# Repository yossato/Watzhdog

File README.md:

# Watzhdog
This device wakes you up when you fall a sleep while you are meeting, studing or working, using a vibration motor.

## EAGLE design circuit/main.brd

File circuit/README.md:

## License  
Copyright (c) 2018, Yoshiaki Sato  
<br />This work is licensed under a <a rel="license" href="http://creativecommons.org/licenses/by-sa/4.0/">Creative Commons Attribution-ShareAlike 4.0 International License</a>.

(c) i.Design Studio 2014
(c) Sparkfun Electronics 2015, 2016

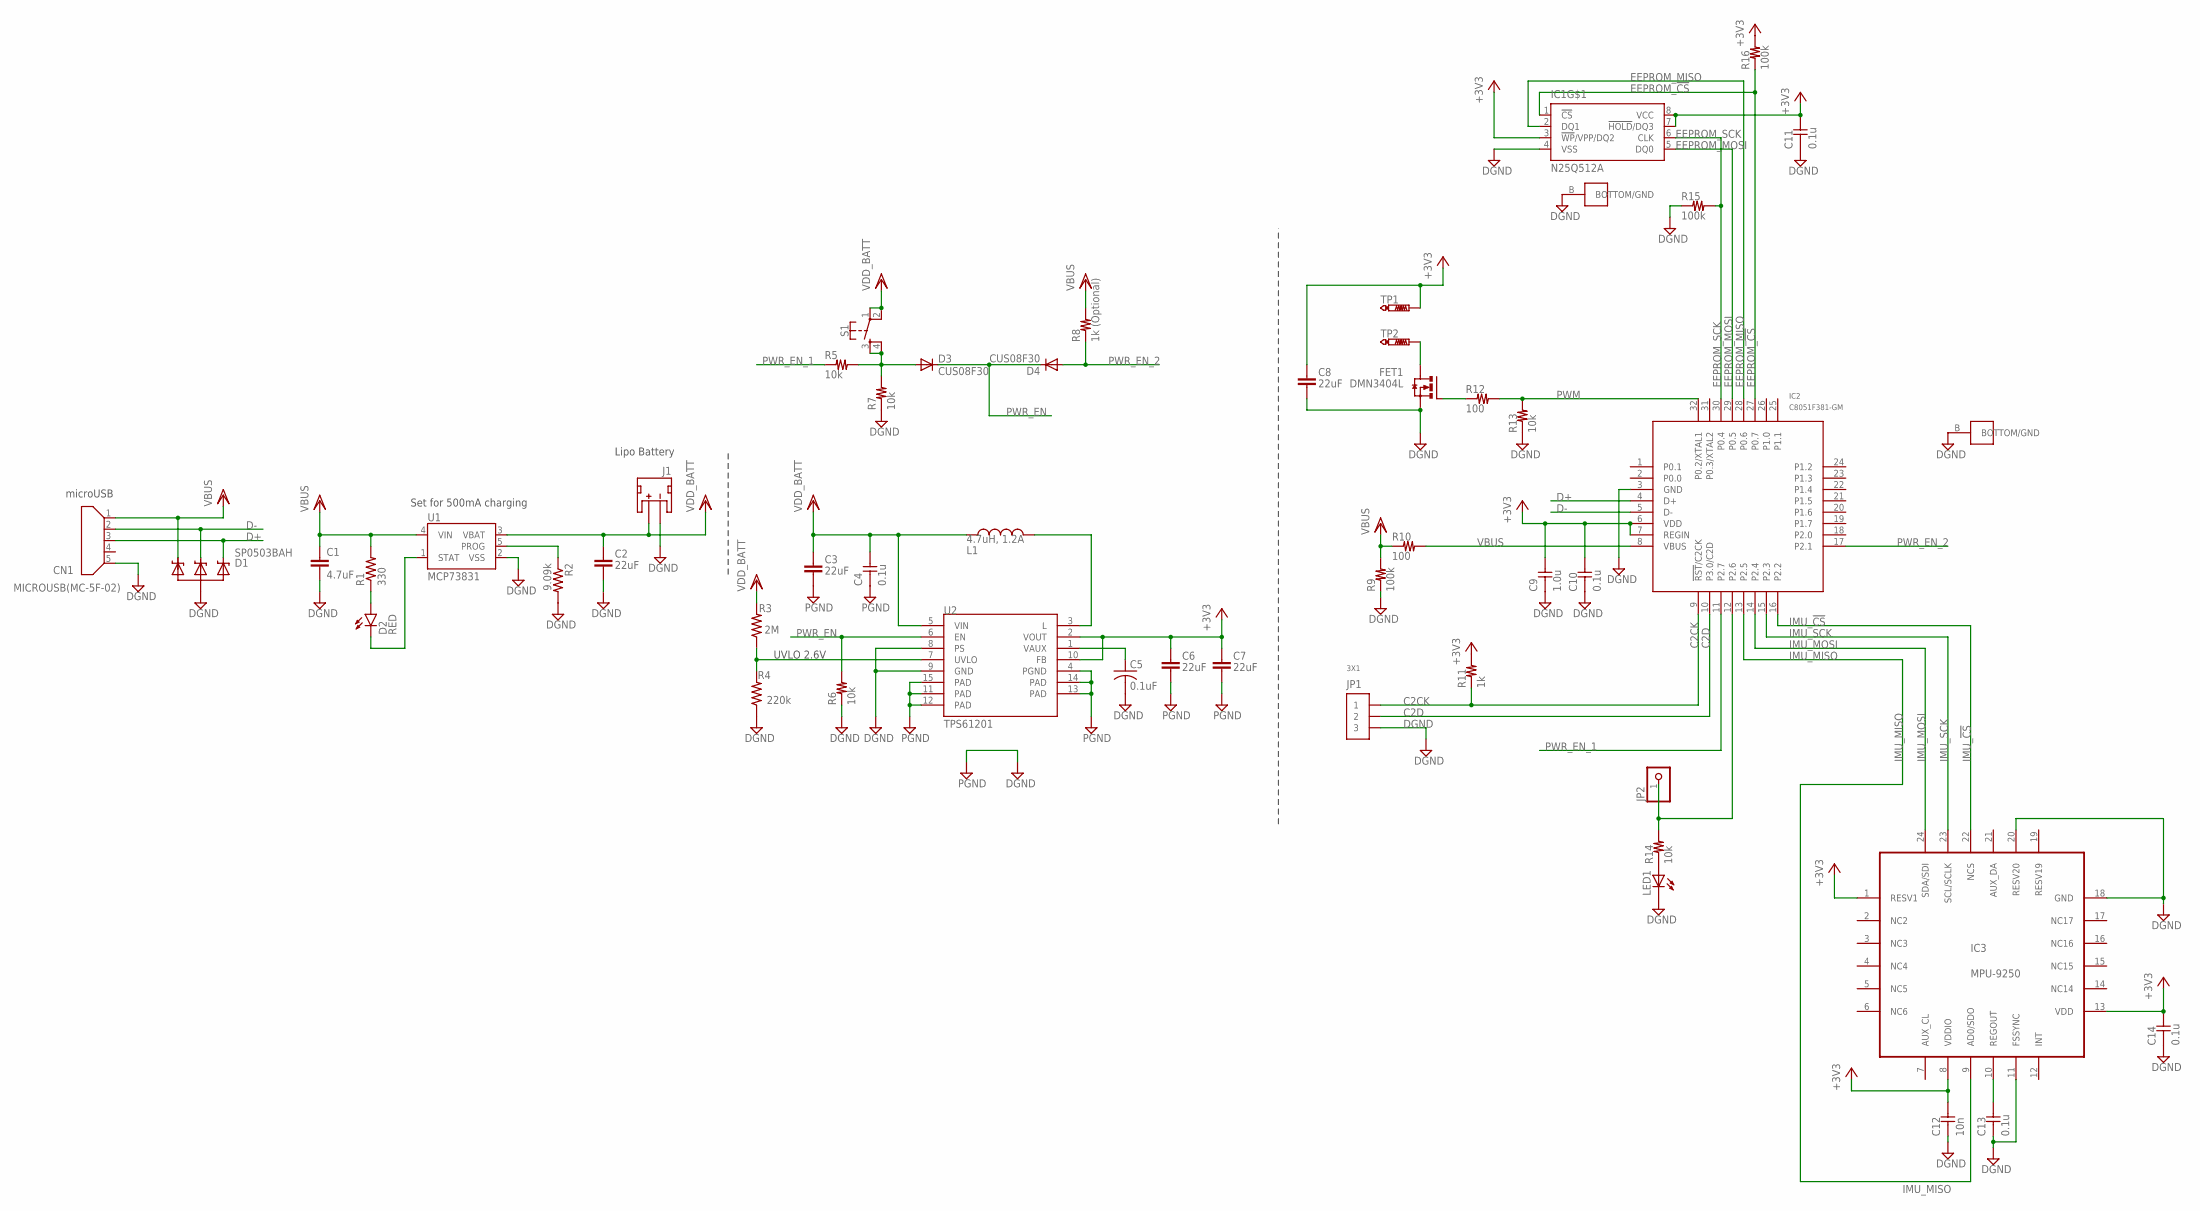
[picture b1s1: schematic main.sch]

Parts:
C1: 4.7uF; 0603-CAP
C2, C3, C6, C7, C8: 22uF; 0805
C4, C10, C11, C13, C14: 0.1u; 1005
C5: 0.1uF; C0402K
C9: 1.0u; 1005
C12: 10n; 1005
CN1: MICROUSB(MC-5F-02)
D1: SP0503BAH; SOT143
D2: RED; LED-0603
D3, D4: CUS08F30; SOD323-W
FET1: DMN3404L; SOT23
IC1: N25Q512A; V-PDFN-8
IC2: C8051F381-GM; QFN32
IC3: MPU-9250; QFN-24
J1: JST; JST-2-SMD
JP1: 3X1; MA3-1
JP2: PINHD-1X1; 1X01
L1: 4.7uH, 1.2A; CDRH2D09
LED1: LED1608O; 1608-OLI
R1: 330; R0402
R2: 9.09k; R0402
R3: 2M; R0402
R4: 220k; R0402
R5, R6, R7, R13, R14: 10k; 1005
R8: 1k (Optional); 1005
R9, R15, R16: 100k; 1005
R10, R12: 100; 1005
R11: 1k; 1005
S1: MOMENTARY-SWITCH-SPST-2-SMD-4.6X2.8MM; TACTILE_SWITCH_SMD_4.6X2.8MM
TP1, TP2: PTR1TP10R; TP10R
U1: MCP73831; SOT23-5
U2: TPS61201; QFN-10_PAD

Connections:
+3V3: C6.1, C7.1, C8.1, C9.P$2, C10.P$2, C11.P$2, C12.P$2, C14.P$2, IC1.3 (!WP!/VPP/DQ2), IC1.7 (!HOLD!/DQ3), IC1.8 (VCC), IC2.6 (VDD), IC2.7 (REGIN), IC3.1 (RESV1), IC3.8 (VDDIO), IC3.13 (VDD), R11.P$2, R16.P$2, TP1.TP, U2.2 (VOUT), U2.10 (FB)
C2CK: IC2.9 (!RST!/C2CK), JP1.1, R11.P$1
C2D: IC2.10 (P3.0/C2D), JP1.2
D+: CN1.3, D1.2, IC2.4 (D+)
D-: CN1.2, D1.3, IC2.5 (D-)
DGND: C1.2, C2.2, C3.2, C4.P$1, C5.2, C6.2, C7.2, C8.2, C9.P$1, C10.P$1, C11.P$1, C12.P$1, C13.P$1, C14.P$1, CN1.5, D1.1, FET1.S, IC1.4 (VSS), IC1.B (BOTTOM/GND), IC2.3 (GND), IC2.B (BOTTOM/GND), IC3.11 (FSSYNC), IC3.18 (GND), IC3.20 (RESV20), J1.1 (-), JP1.3, LED1.K, R2.2, R4.1, R6.P$1, R7.P$1, R9.P$1, R13.P$1, R15.P$1, U1.2 (VSS), U2.4 (PGND), U2.8 (PS), U2.9 (GND), U2.11 (PAD), U2.12 (PAD), U2.13 (PAD), U2.14 (PAD), U2.15 (PAD)
EEPROM_!CS: IC1.1 (!CS), IC2.27 (P0.7), R16.P$1
EEPROM_MISO: IC1.2 (DQ1), IC2.28 (P0.6)
EEPROM_MOSI: IC1.5 (DQ0), IC2.29 (P0.5)
EEPROM_SCK: IC1.6 (CLK), IC2.30 (P0.4), R15.P$2
IMU_!CS: IC2.16 (P2.2), IC3.22 (NCS)
IMU_MISO: IC2.13 (P2.5), IC3.9 (AD0/SDO)
IMU_MOSI: IC2.14 (P2.4), IC3.24 (SDA/SDI)
IMU_SCK: IC2.15 (P2.3), IC3.23 (SCL/SCLK)
LIN: L1.P$1 (1), U2.3 (L)
unnamed: D2.A, R1.1
unnamed: FET1.G, R12.P$1
unnamed: LED1.A, R14.P$1
unnamed: FET1.D, TP2.TP
unnamed: D3.A, R5.P$2, R7.P$2, S1.3, S1.4
unnamed: C13.P$2, IC3.10 (REGOUT)
unnamed: IC2.12 (P2.6), JP2.1, R14.P$2
unnamed: IC2.8 (VBUS), R10.P$2
PROG: R2.1, U1.5 (PROG)
PWM: IC2.32 (P0.2/XTAL1), R12.P$2, R13.P$2
PWR_EN: D3.C, D4.C, R6.P$2, U2.6 (EN)
PWR_EN_1: IC2.11 (P2.7), R5.P$1
PWR_EN_2: D4.A, IC2.17 (P2.1), R8.P$1
STAT: D2.C, U1.1 (STAT)
UVLO: R3.1, R4.2, U2.7 (UVLO)
VAUX: C5.1, U2.1 (VAUX)
VBUS: C1.1, CN1.1, D1.4, R1.2, R8.P$2, R9.P$2, R10.P$1, U1.4 (VIN)
VDD_BATT: C2.1, C3.1, C4.P$2, J1.2 (+), L1.P$2 (2), R3.2, S1.1, S1.2, U1.3 (VBAT), U2.5 (VIN)

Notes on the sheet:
Set for 500mA charging
microUSB
Lipo Battery
UVLO 2.6V

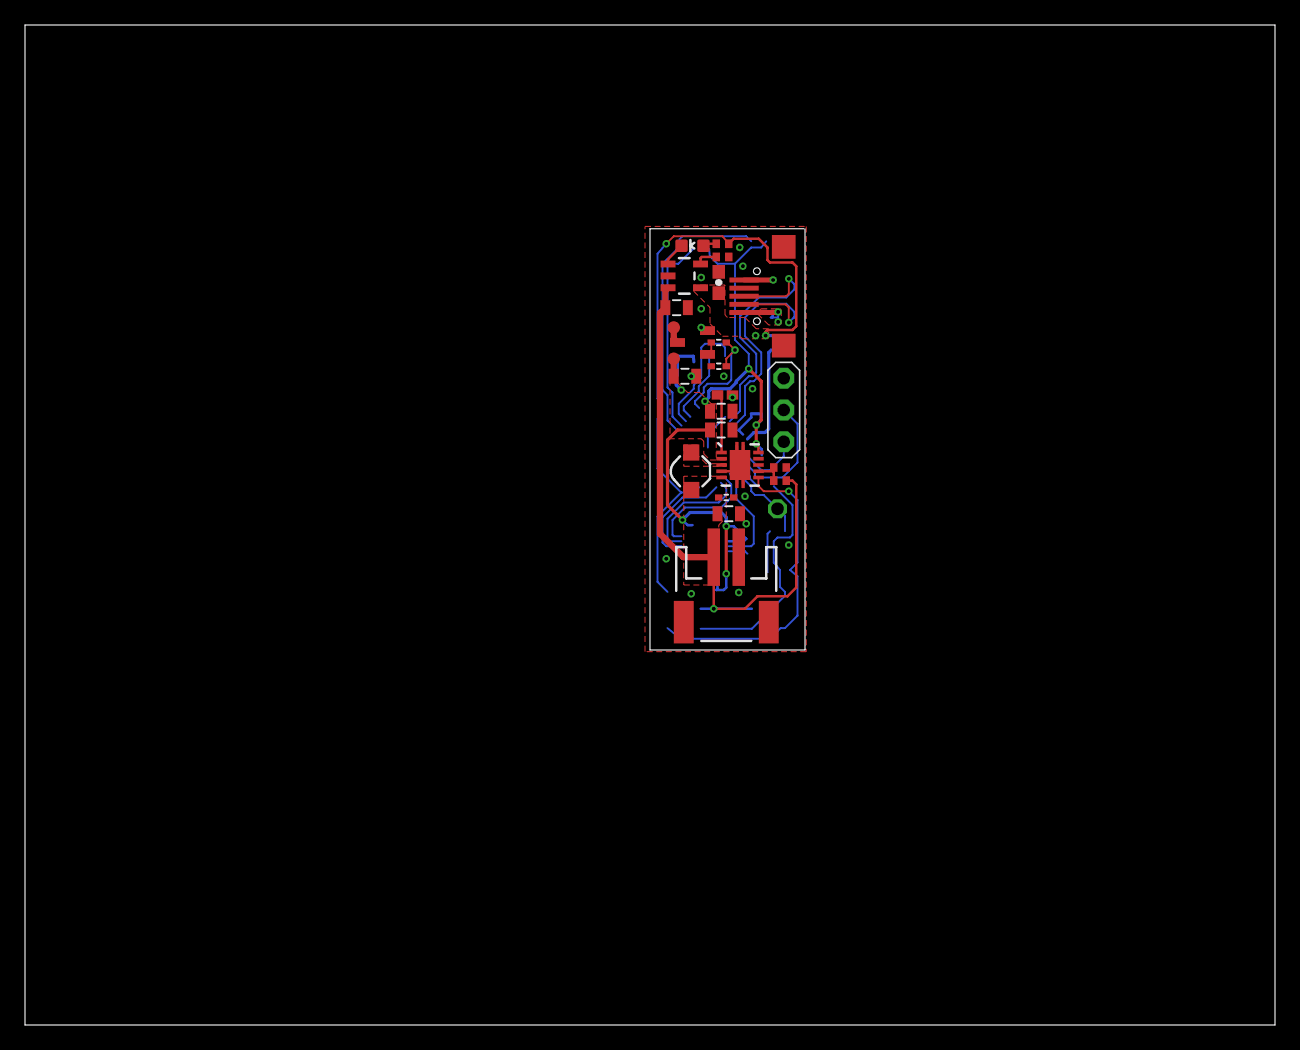
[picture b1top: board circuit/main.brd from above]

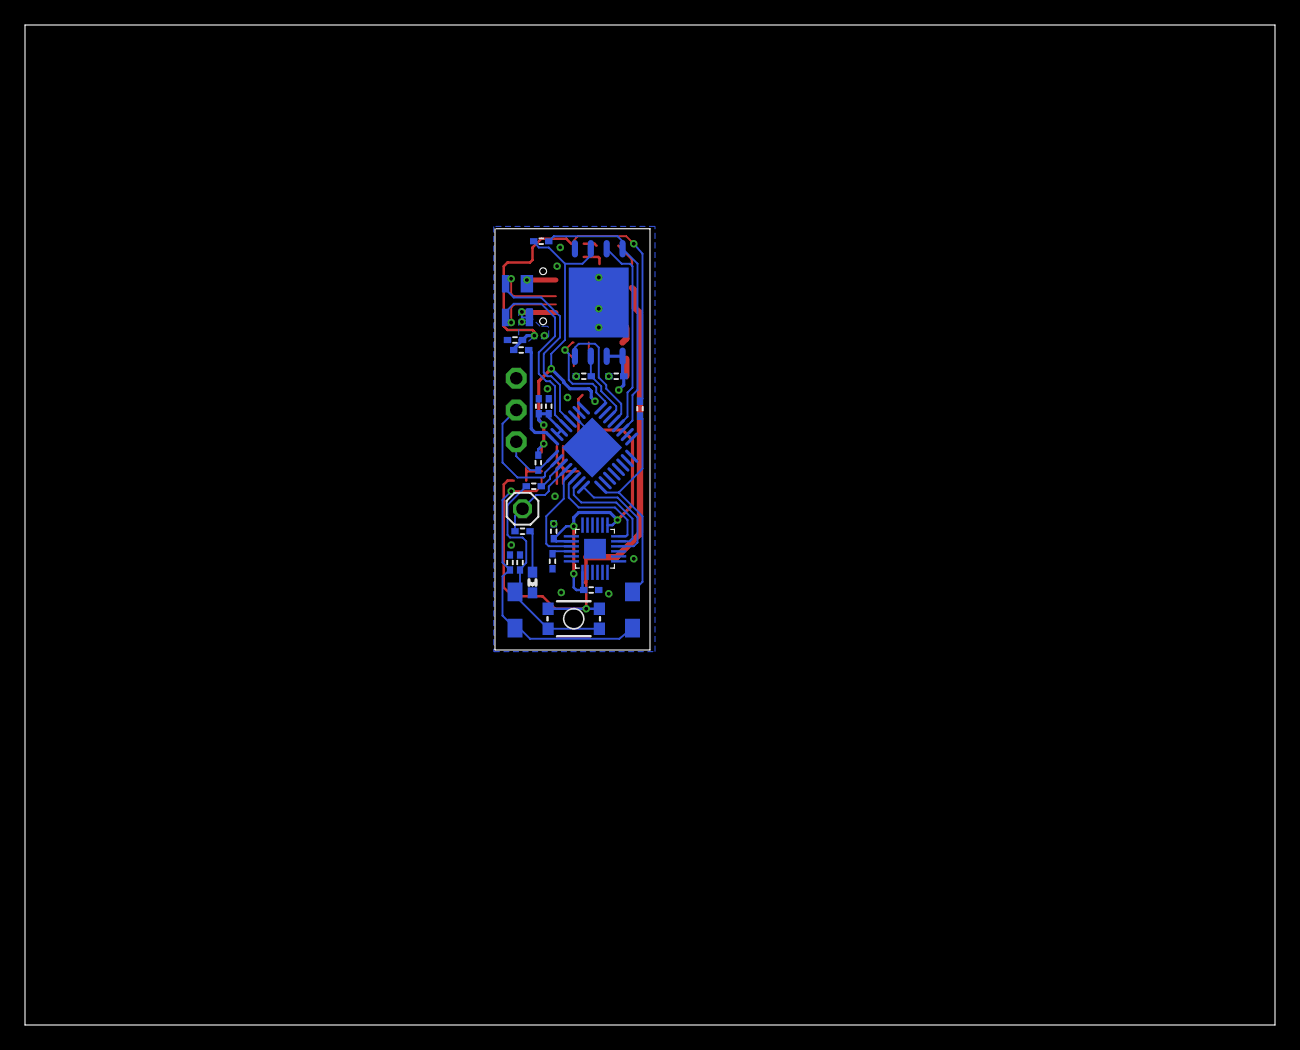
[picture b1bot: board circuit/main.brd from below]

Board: 2 copper layers, 100.0 x 80.0 mm, 49 parts (25 on the bottom side), 33 nets.

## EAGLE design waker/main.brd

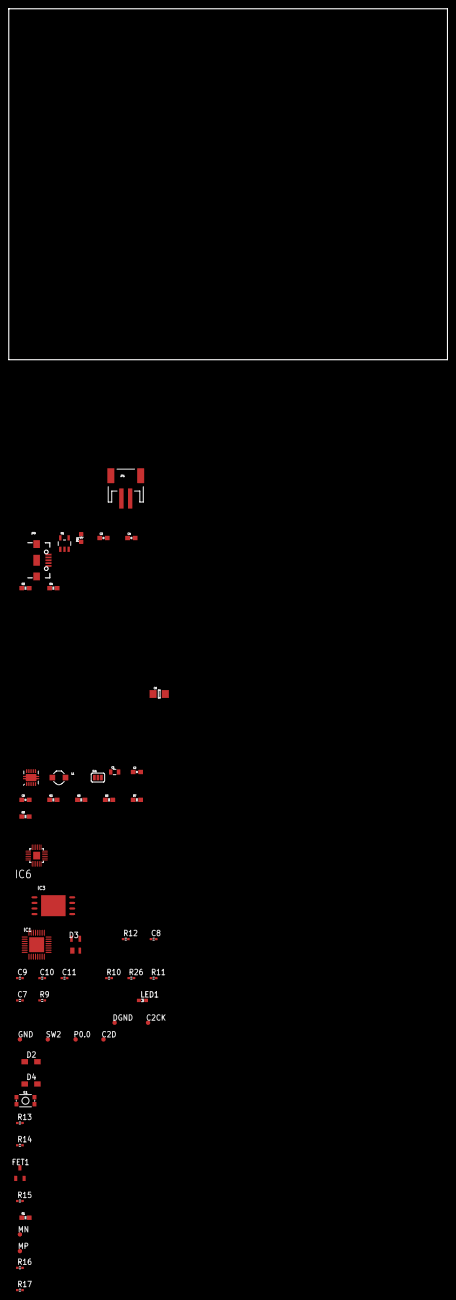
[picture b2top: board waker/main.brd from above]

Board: 2 copper layers, 100.0 x 80.0 mm, 53 parts (0 on the bottom side), 38 nets, no tracks yet.

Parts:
C1: 22uF; 0805
C2, C5: 0.1uF; 0603-CAP
C2CK, C2D: PTR1TP10R; TP10R
C3, C4: 4.7uF; 0603-CAP
C6: 10uF; 1206
C7: 10n; 1005
C8, C9, C11: 0.1u; 1005
C10: 1.0u; 1005
D2, D4: SOD323-W
D3: SP0503BAH; SOT143
D11: RED; LED-0603
DGND: PTR1TP10R; TP10R
FET1: DMN3404L; SOT23
GND: PTR1TP10R; TP10R
IC1: C8051F381-GM; QFN32
IC3: N25Q512A; V-PDFN-8
IC6: MPU-9250; QFN-24
JP1: JST; JST-2-SMD
JP9: Micro USB; USB-AB-MICRO-SMD_V03
L1: 4.7uH, 1.2A; CDRH2D09
LED1: 1608-OLI
MN: PTR1TP10R; TP10R
MP: PTR1TP10R; TP10R
P0.0: PTR1TP10R; TP10R
R1: 0603-RES
R2, R8: 2M; 0603-RES
R3: 330; 0603-RES
R4: 2.0k; 0603-RES
R5, R7: 220k; 0603-RES
R6: 1.2M; 0603-RES
R9, R13, R14, R15, R16: 10k; 1005
R10, R17: 100; 1005
R11, R26: 1k; 1005
R12: 100k; 1005
S1: TACTILE_SWITCH_SMD_4.6X2.8MM
SJ1: SJ_3_PASTE2&3
SW2: PTR1TP10R; TP10R
U1: MCP73831; SOT23-5
U2: TPS61200; QFN-10_PAD

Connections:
3.3V: R6.1, SJ1.1
5V: R8.1, SJ1.3
C2CK: C2CK.TP, IC1.9, R11.P$1
C2D: C2D.TP, IC1.10
D+: D3.2, IC1.4, JP9.D+1
D-: D3.3, IC1.5, JP9.D-1
DGND: C7.P$1, C8.P$1, C9.P$1, C10.P$1, C11.P$1, D3.1, DGND.TP, FET1.S, GND.TP, IC1.3, IC1.B, IC3.4, IC3.B, IC6.11, IC6.18, IC6.20, LED1.K, R12.P$1, R13.P$1, R14.P$1, R15.P$1, R26.P$1
EEPROM_!CS: IC1.27, IC3.1
EEPROM_MISO: IC1.28, IC3.2
EEPROM_MOSI: IC1.29, IC3.5
EEPROM_SCK: IC1.30, IC3.6, R26.P$2
FB: R7.2, SJ1.2, U2.10
GND: C1.2, C3.2, C4.2, C5.2, C6.2, JP1.1, JP9.GND1, R1.2, R4.2, R5.1, R7.1, U1.2, U2.4, U2.8, U2.9, U2.11, U2.12, U2.13, U2.14, U2.15
IMU_!CS: IC1.16, IC6.22
IMU_MISO: IC1.13, IC6.9
IMU_MOSI: IC1.14, IC6.24
IMU_SCK: IC1.15, IC6.23
unnamed: C5.1, U2.1
unnamed: L1.P$1, U2.3
unnamed: D11.A, R3.1
unnamed: IC1.25, SW2.TP
unnamed: IC1.1, R16.P$1
unnamed: D2.C, D4.C, R14.P$2, U2.6
unnamed: D4.A, IC1.2
unnamed: FET1.G, R17.P$1
unnamed: LED1.A, R9.P$1
unnamed: FET1.D, MN.TP
unnamed: D2.A, R13.P$2, R16.P$2, S1.3, S1.4
unnamed: C8.P$2, IC6.10
unnamed: IC1.11, P0.0.TP, R9.P$2
unnamed: IC1.8, R10.P$2
PROG: R1.1, R4.1, U1.5
PWM: IC1.12, R15.P$2, R17.P$2
STAT: D11.C, U1.1
UVLO: C2.2, R2.1, R5.2, U2.7
VBAT: C2.1, C4.1, C6.1, JP1.2, L1.P$2, R2.2, S1.1, S1.2, U1.3, U2.5
VBUS: C3.1, D3.4, JP9.VBUS1, R3.2, R10.P$1, R12.P$2, U1.4
VCC: C1.1, C7.P$2, C9.P$2, C10.P$2, C11.P$2, IC1.6, IC1.7, IC3.3, IC3.7, IC3.8, IC6.1, IC6.8, IC6.13, MP.TP, R6.2, R8.2, R11.P$2, U2.2

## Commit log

2018-04-15 Added circuit schematic
2018-04-16 Added MCU, Gyro and Flash memory
2018-04-16 Midified epf
2018-04-17 Modified circuit
2018-05-04 Put MCU, Gyro and Flash on a board
2018-05-05 Puttin parts
2018-05-06 Modified parts places
2018-05-12 Modified circuit and filename
2018-05-14 Routed some airwires
2018-05-16 Modified parts' position
2018-05-26 Modified board artwork
2018-05-26 Modified dc-dc converter curcuit
2018-05-26 Modified curcuit
2018-05-27 Modified curcuit as a 2-layer board
2018-06-05 Modified parts position
2018-06-06 Zero airwire
2018-06-06 Modified circuit shape
2018-06-13 回路図修正完了 モジュールごとに見やすくした DCDC の高周波ラインを分離 各所パスコン追加 EEPROM のCS ラインにプルアップ追加
2018-06-15 部品配置の再検討中 SW電源，充電IC，USB インターフェース周りは完了 残：モータFET，マイコン，周辺IC
2018-06-17 USBコネクタの角度を変更 ピンヘッダの大きさを再検討
2018-06-17 ピンヘッダのサイズで部品配置を決定する
2018-06-19 GND 以外の配線概ね終了 PGNDとDGND を接合する準備を開始
2018-06-19 PGND，DGND 以外の配線，ポリゴン貼り完了
2018-06-19 airwire 0 本 GND 含めポリゴン貼り完了
2018-06-19 基板サイズ最適化 長さ：37.5mm → 33.7mm 幅：12.7mm → 12.4mm
2018-06-20 シルク調整完了 スペースがないため，すべてを表示できないため，ガーバー出力はしない方が良さそう
2018-06-21 ガーバー発注時（実装サービスあり）のサンプルreadme テキストを追加
2018-06-22 Modified drill hole diameter
2018-06-22 Modified board to enable thermal of polygon
2018-08-03 Uploaded 3D models
2018-08-03 removed unused stuff
2018-08-03 Renamed
2018-08-03 Added firmware directory
2018-08-03 Added license
2018-08-03 Create LICENSE
2018-08-03 Update LICENSE
2018-08-03 Added README.md
2018-08-03 Modified license
2018-08-03 Moved LICENSE
2018-08-03 Added firmware source codes
2018-08-12 Modified PGND air wire
2018-08-12 Removed gerber that contains air wire error
2018-08-12 Moved directory

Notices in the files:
parts and their libraries:
SparkFun-Capacitors: Licensing: Creative Commons ShareAlike 4.0 International - https://creativecommons.org/licenses/by-sa/4.0
